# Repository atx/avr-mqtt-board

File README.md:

avr-mqtt-board
==============

Board with AVR and Ethernet supporting MQTT

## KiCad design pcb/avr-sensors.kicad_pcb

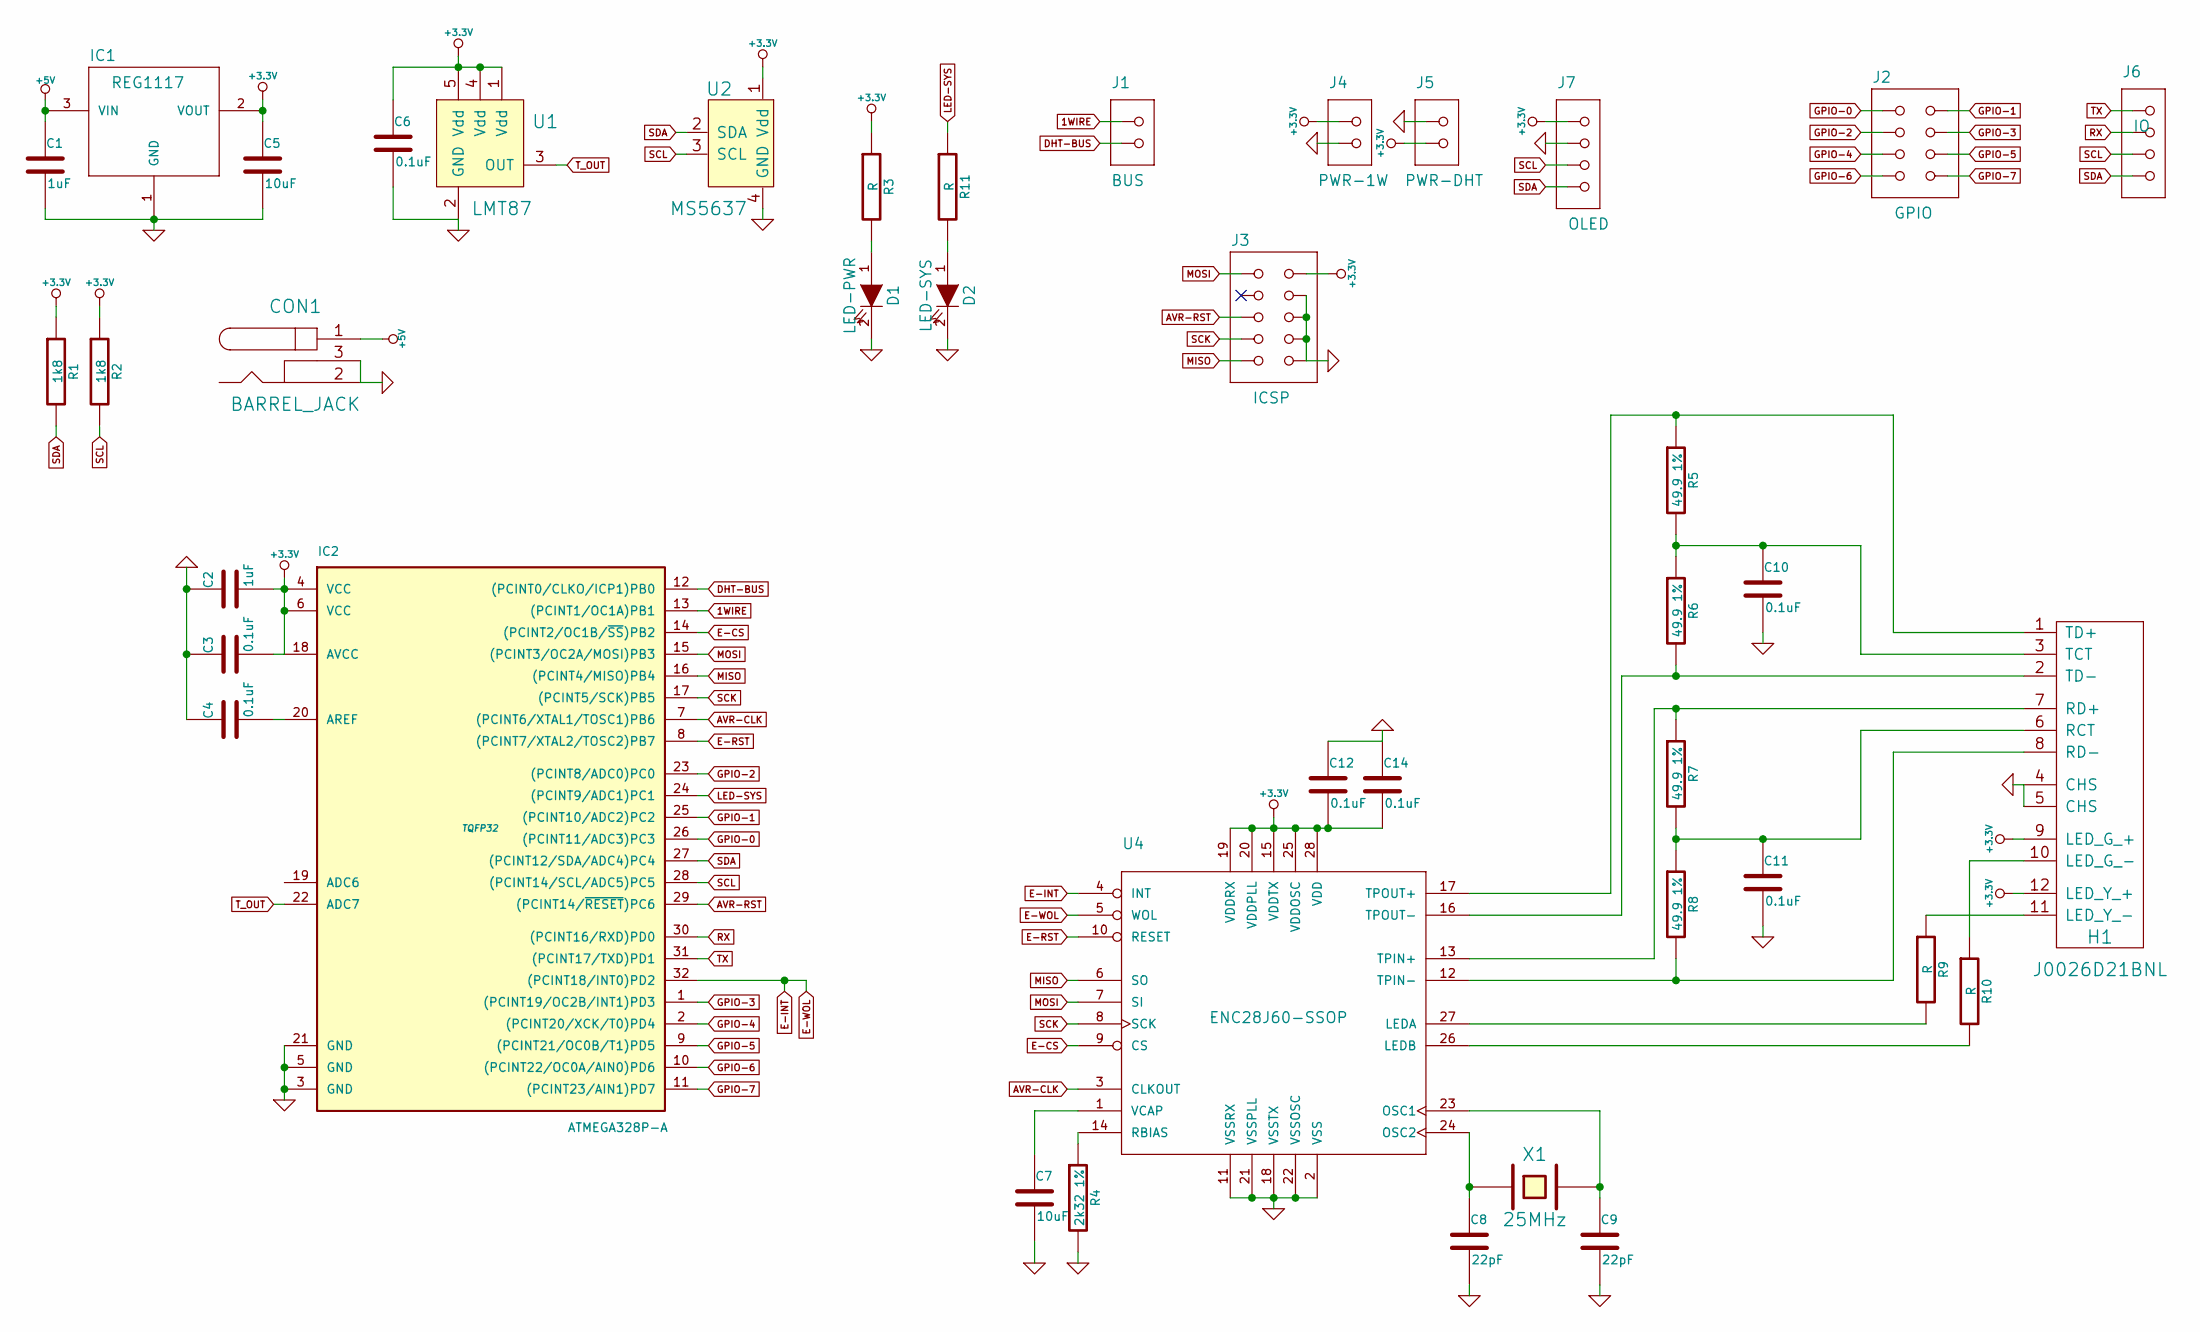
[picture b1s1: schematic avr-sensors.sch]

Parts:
C1, C2: 1uF
C3, C4, C6, C10, C11, C12, C14: 0.1uF
C5, C7: 10uF
C8, C9: 22pF
CON1: BARREL_JACK
D1: LED-PWR
D2: LED-SYS
H1: J0026D21BNL
IC1: REG1117; burr-brown-3-SOT223
IC2: ATMEGA328P-A; TQFP32
J1: BUS; dp_devices-TERMINAL_BLOCK_2P_5
J2: GPIO; dp_devices-M2X4
J3: ICSP; dp_devices-M2X5
J4: PWR-1W; dp_devices-TERMINAL_BLOCK_2P_5
J5: PWR-DHT; dp_devices-TERMINAL_BLOCK_2P_5
J6: IO; dp_devices-M1X4
J7: OLED; dp_devices-M1X4
R1, R2: 1k8
R3, R9, R10, R11: R
R4: 2k32 1%
R5, R6, R7, R8: 49.9 1%
U1: LMT87
U2: MS5637
U4: ENC28J60-SSOP; microchip-enc28j60-SSOP28
X1: 25MHz

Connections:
1WIRE: IC2.13 ((PCINT1/OC1A)PB1), J1.1
+3.3V: C2.2, C3.2, C5.1, C6.1, C12.2, C14.2, H1.9 (LED_G_+), H1.12 (LED_Y_+), IC1.2 (VOUT), IC2.4 (VCC), IC2.6 (VCC), IC2.18 (AVCC), J3.2, J4.1, J5.2, J7.1, R1.1, R2.1, R3.1, U1.1 (Vdd), U1.4 (Vdd), U1.5 (Vdd), U2.1 (Vdd), U4.15 (VDDTX), U4.19 (VDDRX), U4.20 (VDDPLL), U4.25 (VDDOSC), U4.28 (VDD)
+5V: C1.1, CON1.1, IC1.3 (VIN)
AVR-CLK: IC2.7 ((PCINT6/XTAL1/TOSC1)PB6), U4.3 (CLKOUT)
AVR-RST: IC2.29 ((PCINT14/~RESET~)PC6), J3.5
DHT-BUS: IC2.12 ((PCINT0/CLKO/ICP1)PB0), J1.2
E-CS: IC2.14 ((PCINT2/OC1B/~SS~)PB2), U4.9 (CS)
E-INT: IC2.32 ((PCINT18/INT0)PD2), U4.4 (INT), U4.5 (WOL)
E-RST: IC2.8 ((PCINT7/XTAL2/TOSC2)PB7), U4.10 (RESET)
GND: C1.2, C2.1, C3.1, C4.1, C5.2, C6.2, C7.2, C8.2, C9.2, C10.2, C11.2, C12.1, C14.1, CON1.2, CON1.3, D1.2 (K), D2.2 (K), H1.4 (CHS), H1.5 (CHS), IC1.1 (GND), IC2.3 (GND), IC2.5 (GND), IC2.21 (GND), J3.4, J3.6, J3.8, J3.10, J4.2, J5.1, J7.2, R4.2, U1.2 (GND), U2.4 (GND), U4.2 (VSS), U4.11 (VSSRX), U4.18 (VSSTX), U4.21 (VSSPLL), U4.22 (VSSOSC)
GPIO-0: IC2.26 ((PCINT11/ADC3)PC3), J2.1
GPIO-1: IC2.25 ((PCINT10/ADC2)PC2), J2.2
GPIO-2: IC2.23 ((PCINT8/ADC0)PC0), J2.3
GPIO-3: IC2.1 ((PCINT19/OC2B/INT1)PD3), J2.4
GPIO-4: IC2.2 ((PCINT20/XCK/T0)PD4), J2.5
GPIO-5: IC2.9 ((PCINT21/OC0B/T1)PD5), J2.6
GPIO-6: IC2.10 ((PCINT22/OC0A/AIN0)PD6), J2.7
GPIO-7: IC2.11 ((PCINT23/AIN1)PD7), J2.8
LED-SYS: IC2.24 ((PCINT9/ADC1)PC1), R11.1
MISO: IC2.16 ((PCINT4/MISO)PB4), J3.9, U4.6 (SO)
MOSI: IC2.15 ((PCINT3/OC2A/MOSI)PB3), J3.1, U4.7 (SI)
unnamed: C4.2, IC2.20 (AREF)
unnamed: C7.1, U4.1 (VCAP)
unnamed: C8.1, U4.24 (OSC2), X1.1
unnamed: C9.1, U4.23 (OSC1), X1.2
unnamed: C10.1, H1.3 (TCT), R5.2, R6.1
unnamed: C11.1, H1.6 (RCT), R7.2, R8.1
unnamed: D1.1 (A), R3.2
unnamed: D2.1 (A), R11.2
unnamed: H1.1 (TD+), R5.1, U4.17 (TPOUT+)
unnamed: H1.2 (TD-), R6.2, U4.16 (TPOUT-)
unnamed: H1.7 (RD+), R7.1, U4.13 (TPIN+)
unnamed: H1.8 (RD-), R8.2, U4.12 (TPIN-)
unnamed: H1.10 (LED_G_-), R10.1
unnamed: H1.11 (LED_Y_-), R9.1
unnamed: R4.1, U4.14 (RBIAS)
unnamed: R9.2, U4.27 (LEDA)
unnamed: R10.2, U4.26 (LEDB)
RX: IC2.30 ((PCINT16/RXD)PD0), J6.2
SCK: IC2.17 ((PCINT5/SCK)PB5), J3.7, U4.8 (SCK)
SCL: IC2.28 ((PCINT14/SCL/ADC5)PC5), J6.3, J7.3, R2.2, U2.3 (SCL)
SDA: IC2.27 ((PCINT12/SDA/ADC4)PC4), J6.4, J7.4, R1.2, U2.2 (SDA)
TX: IC2.31 ((PCINT17/TXD)PD1), J6.1
T_OUT: IC2.22 (ADC7), U1.3 (OUT)

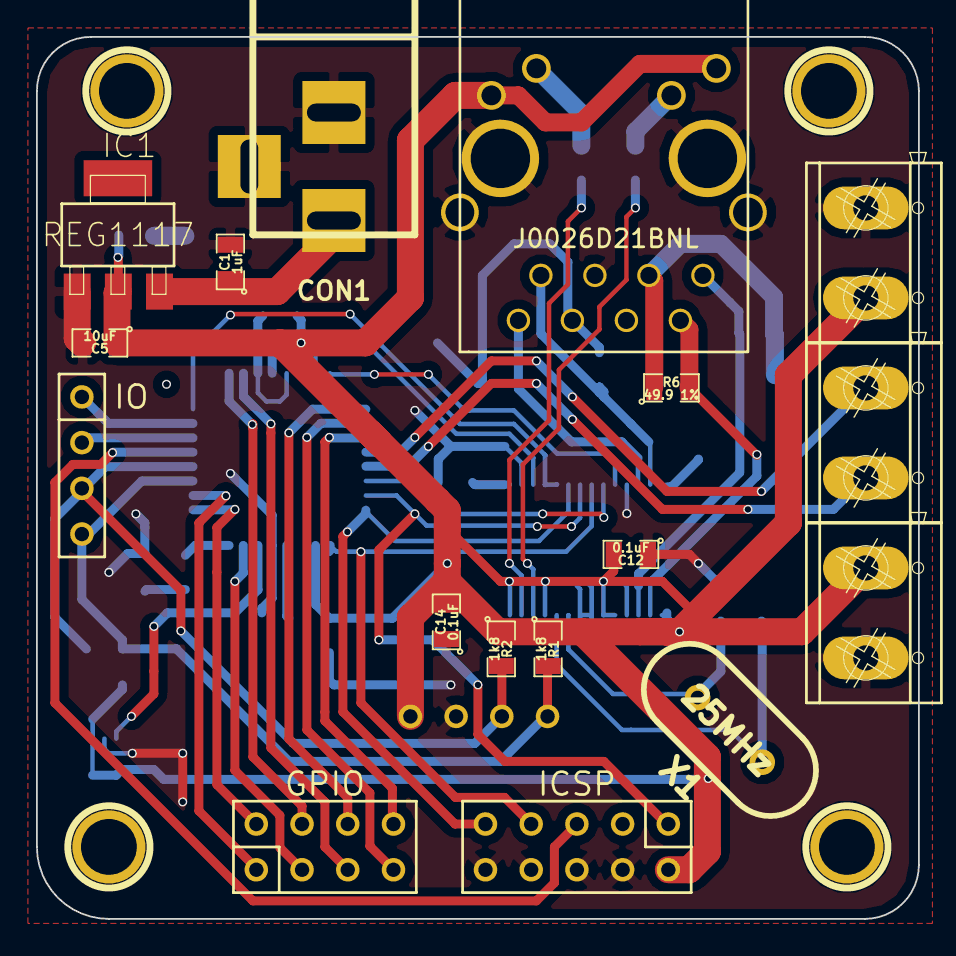
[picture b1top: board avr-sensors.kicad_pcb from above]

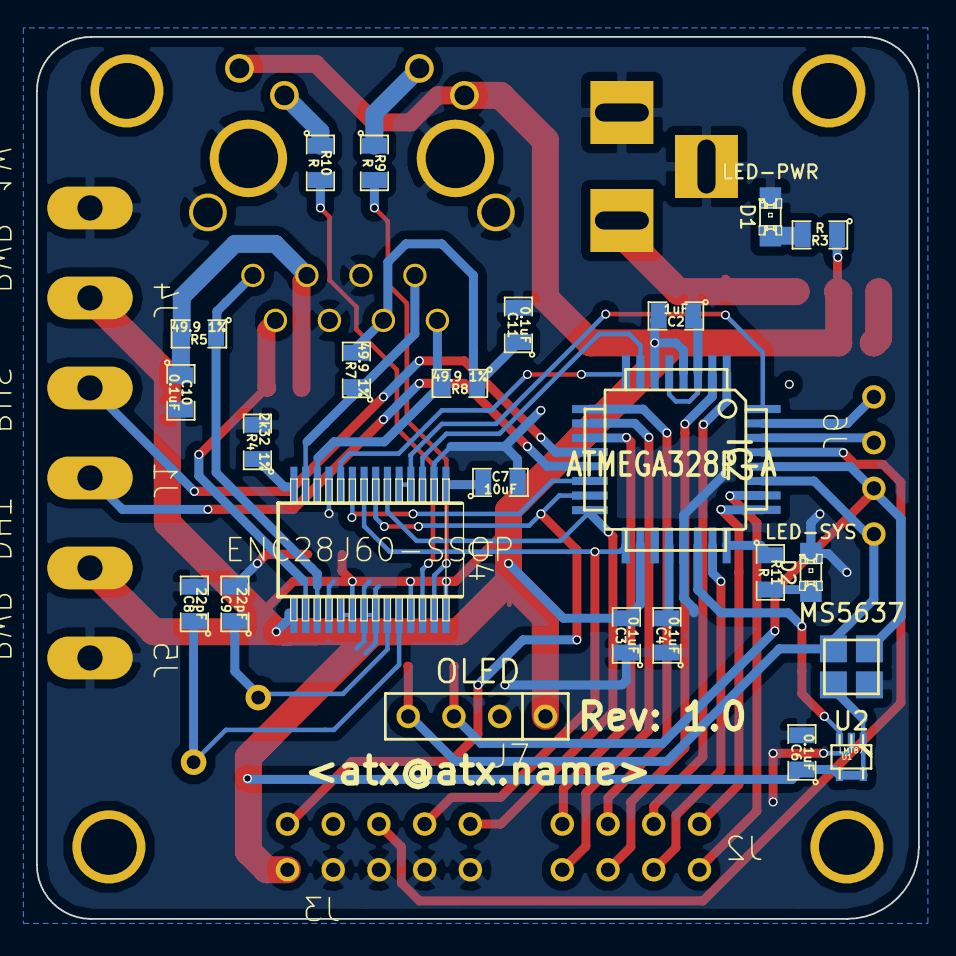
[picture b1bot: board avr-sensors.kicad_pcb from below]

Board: 2 copper layers, 49.0 x 49.0 mm, 41 parts (24 on the bottom side), 44 nets.

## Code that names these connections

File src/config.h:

#ifndef __CONFIG_H__
#define __CONFIG_H__

#include "umqtt/umqtt.h"
#include "nethandler.h"

#define _STR(x) #x
#define STR(x) _STR(x)

#define BUTTON(bank, pin, topic) \
	{ GPIO(bank, pin), topic, 0, false}

#define OUTPUT(bank, pin, topic) \
	{ GPIO(bank, pin), topic }

#define F_CPU		12500000UL

#define IPADDR0		192
#define IPADDR1		168
#define IPADDR2		10
#define IPADDR3		156

#define ETHADDR0		0x00
#define ETHADDR1		0xbd
#define ETHADDR2		0x3b
#define ETHADDR3		0x33
#define ETHADDR4		0x05
#define ETHADDR5		0x71

#define ENC28J60_SPI_PORT		PORTB
#define ENC28J60_SPI_DDR		DDRB
#define ENC28J60_SPI_SCK		PB5
#define ENC28J60_SPI_MOSI		PB3
#define ENC28J60_SPI_MISO		PB4
#define ENC28J60_SPI_SS			PB2
#define ENC28J60_CONTROL_PORT	PORTB
#define ENC28J60_CONTROL_DDR	DDRB
#define ENC28J60_CONTROL_CS		PB2

#define HAS_DHT
#define HAS_DS
#define HAS_BUTTONS
#define HAS_OUTPUTS

#define MQTT_IP0				192
#define MQTT_IP1				168
#define MQTT_IP2				10
#define MQTT_IP3				21

#define MQTT_KEEP_ALIVE			30
#define MQTT_CLIENT_ID			"avr-mqtt-" STR(IPADDR3)
#define MQTT_TOPIC_DATE			"time/date"
#define MQTT_TOPIC_DATETIME		"time/daytime"
#define MQTT_TOPIC_TEMP			"sensors/temperature/frontdoor"
#define MQTT_TOPIC_HUMIDITY		"sensors/humidity/frontdoor"
#define MQTT_TOPIC_WEATHER		"weather/local/general"

#define SENSORS_PUBLISH_RATE	60
#define SENSORS_DISPLAY_RATE	5

#define BUTTONS \
	BUTTON(C, 3, "input/button/doorbell/top"), \
	BUTTON(C, 2, "input/button/doorbell/bottom")

#define OUTPUTS \
	OUTPUT(C, 0, "output/binary/bell")

typedef struct nethandler_state uip_tcp_appstate_t;
#define UIP_APPCALL nethandler_umqtt_appcall

#endif /*__CONFIG_H__*/

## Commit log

2014-08-05 pcb: Added the pcb files
2014-08-05 src: Make the temperature and humidity sensors optional
    By defining HAS_DHT and/or HAS_DS in the config.h file, the firmware can be now
    compiled without support for any of these sensors. This also stops posting the
    sensor information to the corresponding MQTT topic.
2014-08-05 utils: Add the tooled.groovy script
    This script converts provided image to array of bytes suitable for sending to
    the OLED display using functions specified in src/oled.h. The height of the
    converted image does have to be divisible by 8.
    Usage: ./tooled.groovy image1.png image2.png ...
2014-08-05 src: Added support for button inputs
    This feature allows us to watch for falling edge on defined GPIO pins and report
    this to the MQTT broker. The GPIO lines are software debounced and have the
    internall pullups activated on startup.
2014-08-05 src: Added sensors_send()
    The sensors_send (and the sensors_send_* macros) contain common code which was
    previously duplicated in the main function.
2014-08-05 src/main.c: Added binary outputs
    Pins declared as output set state to high/low on receiving MQTT message with
    "true"/"false" as content on their respective topic.
2014-08-05 pcb: Fixed wrong value of the Ethernet termination resistors
    Value was 49k9, corrected to 49.9
2014-08-05 src: Convert simple for loops to use the new times() macro
2014-08-05 .gitignore: Added .map to .gitignore
    .map is a file generated by the build process
2014-08-05 src: Moved subscribe calls to main.c
2014-08-05 src/main.c: Remove extraneous call to display_therm()
    For some reason, the display_therm function was called every time the
    kalive_timer expired.
2014-08-05 src: Initial commit
    Added source files.
2014-08-05 src/main.c: Moved weather parsing/displaying logic to new function
    Previously, the parsing and displaying was done directly in the mqtt message
    handler. This commit moves this part of the code to the newly created
    display_weather function.
2014-08-05 src: Remove unnecesary file deletion in Makefile
    As we are calling GCC only once, there are no intermediate files generated.
2014-08-05 thirdparty: Add submodules
    Added submodules: avr-uip-2 and umqtt
2014-08-05 src/common.h: Added common.h
    common.h contains some miscelleneous preprocessor macros.
2014-08-05 utils/graphic: Add fonts
    Added fonts and images to utils/graphic. These images can be converted to C
    arrays using the tooled.groovy script.
2014-08-05 src/main.c: Changed structure of sensor handling functions
    This commit splits most of the sensor handling code to separate functions. This
    makes the #ifdef-ed parts of the main function slightly more readable.
2014-08-05 src: Disable IP packet reassembly
    We do not need it and it saves around 300 bytes of RAM.
2014-08-05 thirdparty/avr-uip-2: Update to upstream version
2014-08-05 src/main.c: Switched to timer_tryrestart where applicable
2014-08-06 src: Made sensor publish and display rate configurable
    The symbols SENSORS_PUBLISH_RATE and SENSORS_DISPLAY_RATE can be used to
    set the rate at which data from sensors is published and refreshed on the
    display.
2014-08-06 pcb: Fix some pads being only on one side of the PCB
    Pads on the screw terminals and 2.54mm headers were only on one side of the
    PCB.
2014-08-06 pcb: Changed wrong resistor value
    Value of the Ethernet termination resistors used was 49k9 instead of 49.9.
2014-08-06 pcb: Added schematic in PDF format
    Plotted schematic in eeschema to PDF.
2014-08-08 pcb: Changed the value of crystal capacitors to 22pF
    Changed the previously undefined value of the two capacitors connected to the
    25MHz crystal to 22pF.
2014-08-16 enclosure: Add the enclosure DXF file
    Added the .dxf file used to make the enclosure.
2014-08-19 src: Modified the font
    The font used now looks a little bit less ugly.
